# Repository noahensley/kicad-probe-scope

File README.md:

# ESProbeScope3300

A KiCad PCB design created for ETEC 3300. The board is built around the **ESP32-S2FN4R2** and combines USB-C connectivity, 2.4 GHz Wi-Fi (via an on-board chip antenna), a battery charging circuit, an LDO power rail, an audio amplifier, an LCD interface, RGB status LEDs, and a multi-button probe input — all in a single compact design.

---

## Project structure

```
kicad-probe-scope/
├── ESProbeScope3300.kicad_pcb   # PCB layout
├── ESProbeScope3300.kicad_sch   # Schematic
├── ESProbeScope3300.kicad_pro   # Project file
├── sym-lib-table                # Project-scoped symbol library table
│
├── libs/
│   ├── PartsLibrary3300.kicad_sym       # Symbol library
│   └── PartsLibrary3300.pretty/         # Footprint library
│       └── *.kicad_mod
│
├── fab/
│   ├── gerbers/                 # Copper, mask, silkscreen, edge cuts
│   ├── ESProbeScope3300-PTH.drl
│   ├── ESProbeScope3300-NPTH.drl
│   └── ESProbeScope3300-job.gbrjob
│
└── doc/
    ├── schematic.pdf
    └── bom.xlsx
```

---

## Schematic

A PDF export of the schematic is available at [doc/schematic.pdf](doc/schematic.pdf) for viewing without KiCad.

---

## Key components

| Ref | Part | Function |
|-----|------|----------|
| U1 | ESP32-S2FN4R2 | Main MCU with integrated 2.4 GHz Wi-Fi |
| ANT1 | Johanson 2450AT42B100E | 2.4 GHz chip antenna |
| J1 | GCT USB4110-GF-A | USB 2.0 Type-C connector |
| IC3 | MPS MP2664GG | Li-ion battery charger |
| IC1, IC2 | XC8110AA01MR-G | LDO voltage regulators |
| VR1 | ON Semi NCP114ASN330T1G | 3.3 V LDO |
| IC4 | PAM8301 | Class-D audio amplifier |
| LCD1 | Molex 527450897 | LCD flex connector |
| XTAL1 | EXS00A-CS14526 | Crystal oscillator |
| LED1, LED2 | B38G3RGB-10D0003H2U1930 | RGB status LEDs |
| S1–S8 | Alps SKRPABE010 | Tactile pushbuttons |
| SW1 | C&K JS102011SAQN | Slide power switch |
| X3 | — | Probe input header |

---

## Footprint and symbol libraries

All symbols and footprints are in `libs/PartsLibrary3300.kicad_sym` and `libs/PartsLibrary3300.pretty/`. Both are linked via `${KIPRJMOD}` in `sym-lib-table` and the project footprint library table, so they resolve automatically when the project is opened in KiCad regardless of where it is cloned.

Footprints originate from the KiCad standard library, SnapEDA, and manufacturer-published CAD data (Johanson Technology, Walsin, Molex, GCT). Attribution is noted in the footprint description fields within the library files themselves.

---

## License

MIT — see [LICENSE](LICENSE).

---

## Acknowledgements

- [KiCad EDA](https://www.kicad.org/) and the KiCad Libraries contributors
- [SnapEDA](https://www.snapeda.com) for component models
- Johanson Technology, Walsin Technology, Molex, GCT, and other component manufacturers for publishing CAD data

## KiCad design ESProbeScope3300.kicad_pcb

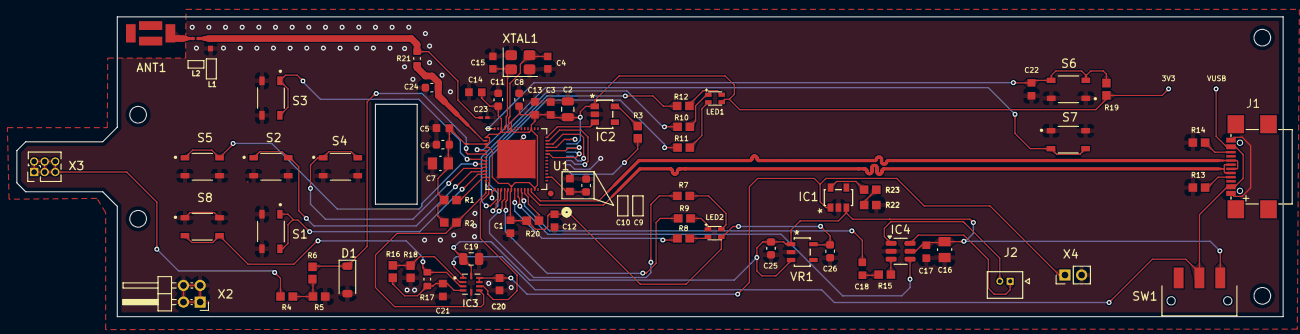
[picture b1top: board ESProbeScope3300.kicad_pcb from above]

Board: 2 copper layers, 152.1 x 36.0 mm, 77 parts (1 on the bottom side), 59 nets.

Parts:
ANT1: ANT_2450AT42B100E; ANT_2450AT42B100E_JOT
C1, C3, C5, C10, C12, C13, C14, C17, C18, C21, C22: 0.1uF; CAP_0603_X_WAL
C2, C19: 10uF; C_0805_2012Metric
C4, C15: 15pF; CAP_0603_S_WAL
C6, C9, C11, C25, C26: 1uF; C_0603_1608Metric
C7, C16: 10uF; CAP_GMC21_1.50H_CCE
C8: 100pF; C_0603_1608Metric
C20: 4.7uF; CAPC1608X90N
C23: 1pF; CAP_GMC02_CCE
C24: DNP; C_0603_1608Metric
D1: DDZ9684Q-7; D_SOD-123
IC1, IC2: XC8110AA01MR-G
IC3: MP2664GG-0000-Z; QFN50P200X200X105-10N
IC4: PAM8301; SOT-23-6
J1: USB4110-GF-A
J2: MOLEX 53047-02; MOLEX_530470210
L1: 1.5nH; IND_L-07C3N3SV6T_JOT
L2: 3.3nH; L_0201_0603Metric
LCD1: 527450897; CONN_527450897_MOL
LED1, LED2: B38G3RGB-10D0003H2U1930; B38G3RGB-10D0003H2U1930_0606_RGB_LED
R1, R2, R5, R16, R18, R19, R20: 10k; RESC1607X60N
R3: 22R; RESC1607X60N
R4, R15, R22, R23: 100k; RESC1607X60N
R6, R7, R8, R9, R10, R11, R12: 1k; RESC1607X60N
R13, R14: 5.1k; RESC1607X60N
R17: 300k; RESC1608X55N
R21: 0R; RESC1608X55N
S1, S2, S3, S4, S5: SKRPABE010; SW_SKRPABE010
S6: SW_RST; SW_SKRPABE010
S7: SW_BOOT; SW_SKRPABE010
S8: SW_PWR; SW_SKRPABE010
SW1: JS102011SAQN; SW_JS102011SAQN
U1: ESP32-S2FN4R2; ESP32-S2FN4R2_QFN56
VR1: NCP114ASN330T1G; NCP114ASN330T1G_5-TSOP
X2: TEST; PinHeader_2x02_P2.00mm_Horizontal
X3: PROBE; PinHeader_2x03_P1.27mm_Vertical
X4: Conn_01x02; PinHeader_1x02_P2.00mm_Vertical
XTAL1: EXS00A-CS14526; Crystal_SMD_WE_CFPX-180-4Pin_3.2x2.5mm

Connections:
DCP_1: C1.1, C2.1, C3.1, C5.1, C6.1, C7.1, C8.1, C11.1, C12.1, C13.1, C14.1, C26.1, IC2.1 (VIN), LCD1.7 (VDD), LED1.3, LED2.3, R1.1, R2.1, R19.1, R20.2, U1.1 (VDDA0), U1.3 (VDD3P3_1), U1.4 (VDD3P3_2), U1.20 (VDD3P3_RTC), U1.27 (VDD3P3_RTC_IO), U1.45 (VDD3P3_CPU), U1.51 (VDDA1), U1.54 (VDDA2), VR1.5 (OUT)
DCP_30: C9.1, C10.1, U1.30 (VDD_SPI)
EN: C22.1, R19.2, S6.3, S6.4, U1.56 (CHIP_PU)
GND: C1.2, C2.2, C3.2, C4.2, C5.2, C6.2, C7.2, C8.2, C9.2, C10.2, C11.2, C12.2, C13.2, C14.2, C15.2, C16.2, C17.2, C19.2, C20.2, C21.2, C22.2, C23.2, C24.2, C25.2, C26.2, D1.2 (A), IC1.2 (VSS), IC2.2 (VSS), IC3.5 (GND), IC4.2 (GND), J1.A1B12 (GND), J1.B1A12 (GND), L1.2, LCD1.2 (GND), R5.2, R13.1, R14.1, R18.2, R22.2, S1.3, S1.4, S2.3, S2.4, S3.3, S3.4, S4.3, S4.4, S5.3, S5.4, S6.1, S6.2, S7.1, S7.2, S8.1, S8.2, U1.57 (GND), VR1.2 (GND), X2.1, X2.2, X2.3, X2.4, X4.2, XTAL1.2, XTAL1.4
IO0: S7.3, S7.4, U1.5 (GPIO0)
IO1: D1.1 (K), R6.1, U1.6 (GPIO1)
IO3: S3.1, S3.2, U1.8 (GPIO3)
IO4: S5.1, S5.2, U1.9 (GPIO4)
IO5: S4.1, S4.2, U1.10 (GPIO5)
IO6: S2.1, S2.2, U1.11 (GPIO6)
IO7: S1.1, S1.2, U1.12 (GPIO7)
IO8: IC3.7 (SDA), R1.2, U1.13 (GPIO8)
IO9: IC3.6 (SCL), R2.2, U1.14 (GPIO9)
IO10: R12.1, U1.15 (GPIO10)
IO11: R10.1, U1.16 (GPIO11)
IO12: R11.1, U1.17 (GPIO12)
IO13: R7.1, U1.18 (GPIO13)
IO14: R9.1, U1.19 (GPIO14)
IO15: R8.1, U1.21 (GPIO15/XTAL_32K_P)
IO16: IC4.4 (~SD), U1.22 (GPIO16/XTAL_32K_N)
IO17: C18.2, U1.23 (GPIO17/DAC_1)
IO18: R20.1, U1.24 (GPIO18/DAC_2)
IO33: LCD1.5 (SDA), U1.37 (GPIO33)
IO34: LCD1.6 (SCL), U1.38 (GPIO34)
IO35: LCD1.8 (CS), U1.39 (GPIO35)
IO36: LCD1.4 (RS), U1.40 (GPIO36)
IO37: LCD1.3 (RESET), U1.41 (GPIO37)
IO38: IC2.3 (CE), U1.42 (GPIO38)
LAN_IN: C24.1, R21.2, U1.2 (LNA_IN)
unnamed: ANT1.1, L2.1
unnamed: C18.1, R15.2
unnamed: C23.1, L1.1, L2.2, R21.1
unnamed: IC1.5 (VOUT), R23.1
unnamed: IC2.5 (VOUT), R3.1
unnamed: IC3.3 (INT), R17.2, S8.3, S8.4
unnamed: IC3.2 (NTC), R16.2, R18.1
unnamed: C21.1, IC3.4 (VDD), R16.1, R17.1
unnamed: IC4.3 (IN), R15.1
unnamed: IC4.6 (OUT+), J2.1
unnamed: IC4.1 (OUT-), J2.2
unnamed: J1.A5 (CC1), R13.2
unnamed: J1.B5 (CC2), R14.2
unnamed: LCD1.1 (LEDA), R3.2
unnamed: LED1.1, R10.2
unnamed: LED1.2, R11.2
unnamed: LED1.4, R12.2
unnamed: LED2.1, R9.2
unnamed: LED2.2, R8.2
unnamed: LED2.4, R7.2
unnamed: R4.2, R5.1, R6.2
unnamed: R22.1, R23.2
unnamed: R4.1, X3.1, X3.2, X3.3, X3.4, X3.5, X3.6
USBD+: J1.A6 (D+), J1.B6 (D+), U1.26 (GPIO20)
USBD-: J1.A7 (D-), J1.B7 (D-), U1.25 (GPIO19)
VBAT: C20.1, IC1.1 (VIN), IC3.8 (BAT1), IC3.9 (BAT2), X4.1
VSYS: C16.1, C17.1, C19.1, C25.1, IC1.3 (CE), IC3.10 (SYS), IC4.5 (VDD), SW1.3, VR1.1 (IN), VR1.3 (EN)
VUSB: IC3.1 (IN), J1.A4B9 (VBUS_0), J1.B4A9 (VBUS_1), SW1.2
XIN: C4.1, U1.52 (XTAL_N), XTAL1.3
XOUT: C15.1, U1.53 (XTAL_p), XTAL1.1

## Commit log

2026-05-12 Initial commit of project files.
2026-05-12 Modified structure, added README and License information.
2026-05-12 Added schematic PDF.
2026-05-12 Added reference to schematic PDF.
